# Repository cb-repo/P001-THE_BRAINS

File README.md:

# THE BRAINS v4.0

THE BRAINS is an compact and lightweight dual DC-motor ESC: originally designed for antweight combat robots, but is suitable for any appliction requiring a lightweight motor driver.

Designed and built in [Christchurch, New Zealand ](https://www.google.co.nz/maps/place/Christchurch+New+Zealand) by Connor Benton, visit [cb-technology](https://www.cb-technology.co.nz/) for details.

## FEATURES

- 2x Bi-Directional DC motor outputs.
- 2x Signal output channels for additional electroncis (BLDC ESC, servo, etc).
- Status LED's to indicate run mode, faults and calibration.
- Under-voltage, over-current, over-temperature, and reverse polarity protections.
- Internal BEC to provide power to the radio reciever.
- Failsafe checks for loss of connection with radio.
- Auto-Detection of different radio protocols on the same input.
- Instant brown-out recovery.
- Calibrate function to customise drive mode, channel mapping, and channel inversion.
- Includes a 100nF capacitor across each motor to filter noise and voltage spikes.

## SPECIFICATIONS

- **Dimensions:** 25x19x3 mm
- **Weight:** 2g *excluding wires*
- **Input Voltage - Rated:** 2S lipo (6-10.4V)
- **Input Voltage - Max:** 12.0V
- **Motor Output:** 2.1A cont (3A peak) per channel 
- **BEC:** 5V, 80mA. Designed to power the radio reciever but no motors or servos
- **Signal Input:** Servo PWM, PPM, IBUS, SBUS
- **Signal Mixing:** Onboard signal mixing for TANK/ARCADE drive styles and channel mapping + inverting
- **Signal Output:** Servo PWM 
   
## Status LEDs
There are two LEDs on THE BRAINS (1x red, 1x green) and the behaviour of each indicate what state the device is in.
 - **Normal Operation** Green: ON, Red: OFF
 - **Fault Conditions**
    - **Signal-Input** Green: FLASH, Red: OFF
    - **Under-Voltage** Green: OFF, Red: FLASH (1Hz)
    - **Over-Temperature** Green: OFF, Red: FAST FLASH (5Hz)
 - **Calibration** Green: PATTERN, Red: PATTERN. (See Calibration section for specific LED patterns) 

## Fault Conditions
In all of the following fault conditions, all drive/output signals are stopped no matter the input signals. Once the fault condition is resolved, functionality will resume immediately. 
 - **Under-Voltage:** An under-voltage event occurs if the battery voltage falls below 3.2V (per cell). 
 - **Over-Temperature:** An over-temperature event occurs when the temperature sense circuit on THE BRAINS reaches 100°C.
 - **Signal-Input:** A signal-input fault occurs if the signal between the THE BRAINS and the radio reciever is lost. Note: You still need to set the failsafe on the radio reciever to detect loss of connection with the transmitter.

## Calibration
###### Calibration Parameters
THE BRAINS has a number of calibration parateters that are can be chosen from, these are:
- **Input Signal:**
At no point should the operator have to manually set the protocol, this will be auto-detected without the operator knowing.
    - Servo PWM (standard 1-2ms pulse)
    - PPM
    - IBUS
    - SBUS
- **Driving Mode:**
    - Tank (Each motor speed is controlled by a different input)
    - Arcade (One input controls both motor speeds and another is mixed in to control the steering) 
- **Signal Mapping:**
    - Any input channel can be mapped to any of the 4 outputs (2x motors + 2x signal output). 
    - Any channel can be reversed (usually auto-detected during the calibration procedure). 

The default calibration parameters are:
- **Input Signal:** SBUS
- **Driving Mode:** TANK
- **Signal Mapping:** 
     - Ch1 = Motor1, 
     - Ch2 = Motor2,
     - Ch3 = Servo1,
     - Ch4 = Servo2,

###### Calibration Procedure
 1. Ensure the transmitter is turned ON, it has been bound to the radio reciever, and all sticks are in their zero (neutral) position.

 2. Plug the radio reciever and motors into THE BRAINS. 
 It is important that the motors are connected in the orientation used for the final robot, this will allow auto-detection of the channel mapping and inversion during the following Simon-says process.

 3. Turn THE BRAINS ON and, within 10 seconds, trigger the calibration procedure using one of the following:
    - Short-circuit the two calibration pads on the underside. 
    These pads are the two circular pads close together and circled with silkscreen.
    - Wiggle any input on the transmitter back and forward 10 times. 
    Make sure to push the stick from CENTER all the way to MAX/MIN when wiggling. 

 4. Both status LEDs will pulse 10 times and then stay fully illumintaed to indicated THE BRAINS has entered CALIBRATION mode and is ready to begin the Simon-Says process. 

 5. When ready, push any stick on the transmitter to MAX and back to CENTER.
 The rest of the calibration happens pretty quickly so please read, and understand, steps 6 + 7 before proceeding. 

 6. Both status LED's will turn OFF and the Simon-says motor calibration procedure is started. 
    - Two tests are run, each will twitch the two motors and cause the robot to move forward, reverse, left, or right. 
    The user must then input that motion back into the remote. eg:
        - Robot twitches forward: Tank drive, simualtaneously push both sticks forward. Arcarde drive, push one stick forward.
        - Robot twitches left: Tank drive, simualtaneously push left stick back and right forward. Arade drive, push one stick left
    - The process for each test is:
        1. Both LED's turn OFF
        2. The motor twitches
        3. Red LED turns ON
        4. User presses input(s) to MAX/MIN
        5. Green LED turns ON 
        6. User returns input(s) back to CENTER
        7. Both LED's pulse 3 times to indicate success
        8. Repeat for second test

 7. Both status LED's will again turn OFF and the Simon-says output signal calibration procedure is started. 
    - Two more tests are run to map the inputs to the Signal 1 and 2 outputs. The primary difference with this test is that no motor are driven, THE BRAINS is just monitoring the inputs.
    - The process for each test is:
        1. Both LED's will momentrarily turn OFF to indicate the test has started
        2. Red LED turns ON
        3. User presses the input (to MAX/MIN) they want mapped to output signal 1
        4. Green LED turns ON
        5. User returns input back to CENTER 
        6. Both LED's pulse 3 times to indicate success
        7. Repeat for output signal 2.

 12. Calibration Complete
     - Both status LEDs will pulse 10 times to indicate a successfull calibration.
     - Once the LED pulses are complete, THE BRAINS immediately enter Run mode with the new calibration.
     - If THE BRAINS is turned OFF before completing the calibration process, NONE of the new parameters are stored and it will revert to the previous configuraion.

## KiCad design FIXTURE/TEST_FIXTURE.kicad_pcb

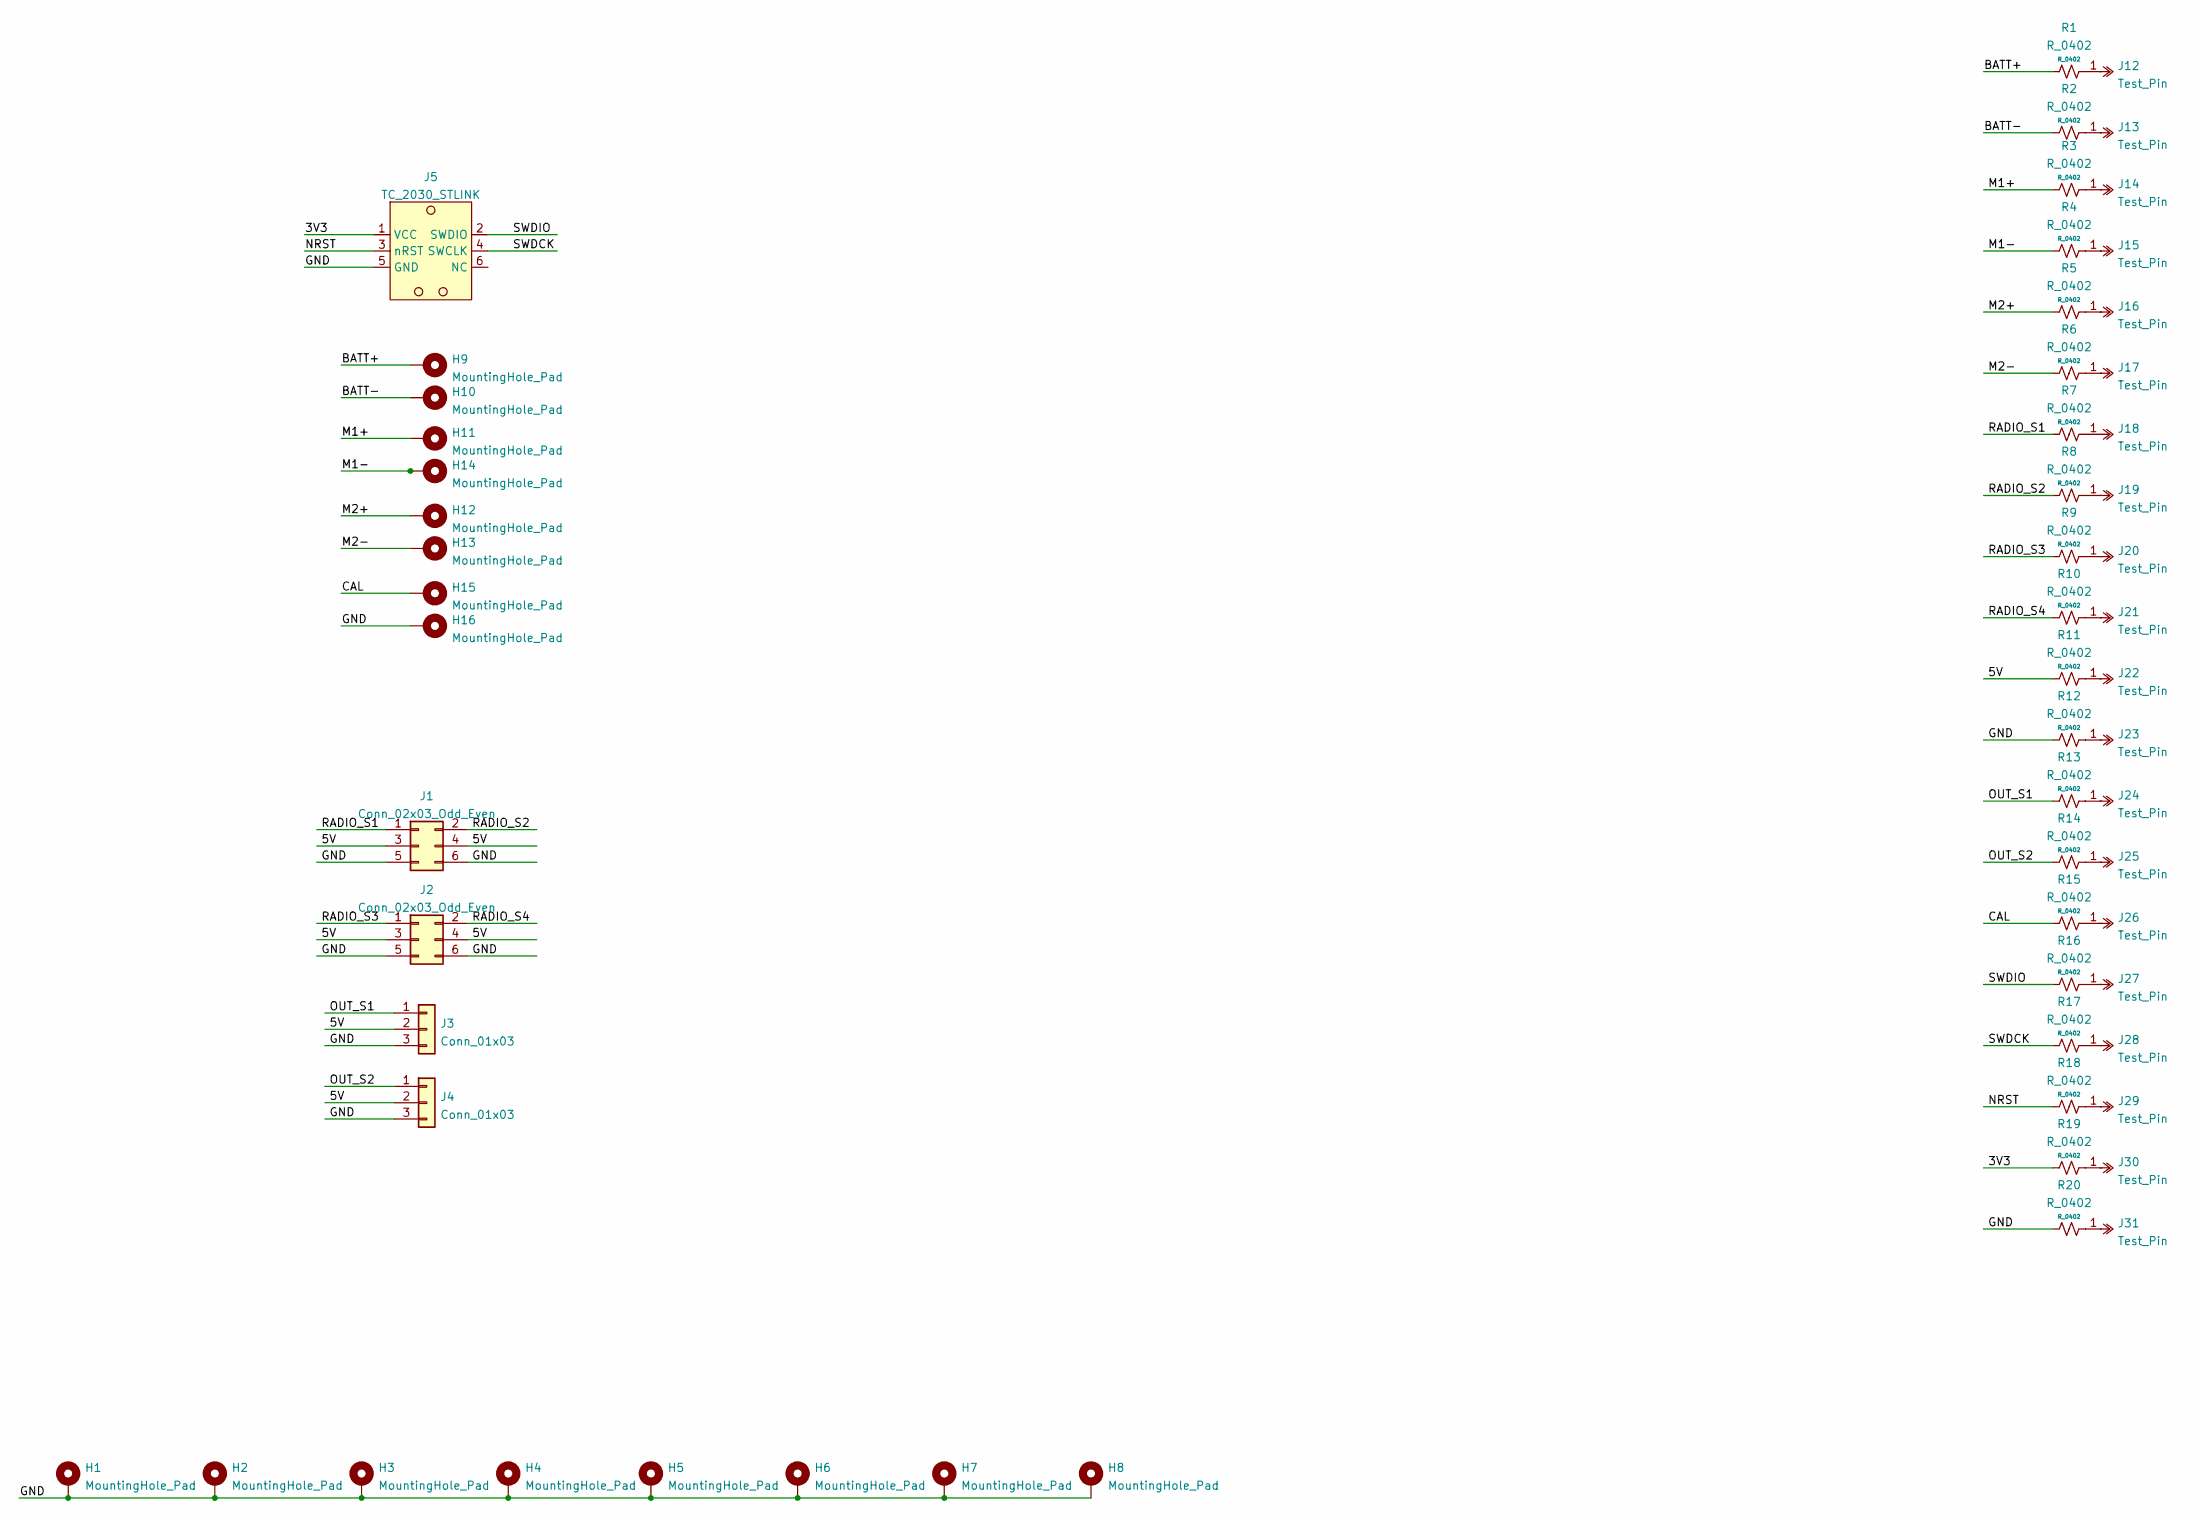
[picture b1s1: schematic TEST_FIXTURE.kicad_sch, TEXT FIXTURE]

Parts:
H1, H2, H3, H4, H5, H6, H7, H8, H9, H10, H11, H12, H13, H14, H15, H16: MountingHole_Pad; MountingHole_3mm_Pad_TopBottom
J1, J2: Conn_02x03_Odd_Even; PinHeader_2x03_P2.54mm_Vertical
J3, J4: Conn_01x03; PinHeader_1x03_P2.54mm_Horizontal
J5: TC_2030_STLINK; Tag-Connect_TC2030-IDC-FP_2x03_P1.27mm_Vertical
J12, J13, J14, J15, J16, J17, J18, J19, J20, J21, J22, J23, J24, J25, J26, J27, J28, J29, J30, J31: Test_Pin; R-2-SC
R1, R2, R3, R4, R5, R6, R7, R8, R9, R10, R11, R12, R13, R14, R15, R16, R17, R18, R19, R20: R_0402

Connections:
/3V3: J5.1 (VCC), R19.1
/5V: J1.3, J1.4, J2.3, J2.4, J3.2, J4.2, R11.1
/BATT+: H9.1, R1.1
/BATT-: H10.1, R2.1
/CAL: H15.1, R15.1
/GND: H1.1, H2.1, H3.1, H4.1, H5.1, H6.1, H7.1, H8.1, H16.1, J1.5, J1.6, J2.5, J2.6, J3.3, J4.3, J5.5 (GND), R12.1, R20.1
/M1+: H11.1, R3.1
/M1-: H14.1, R4.1
/M2+: H12.1, R5.1
/M2-: H13.1, R6.1
/NRST: J5.3 (nRST), R18.1
/OUT_S1: J3.1, R13.1
/OUT_S2: J4.1, R14.1
/RADIO_S1: J1.1, R7.1
/RADIO_S2: J1.2, R8.1
/RADIO_S3: J2.1, R9.1
/RADIO_S4: J2.2, R10.1
/SWDCK: J5.4 (SWCLK), R17.1
/SWDIO: J5.2 (SWDIO), R16.1
unnamed: J12.1, R1.2
unnamed: J13.1, R2.2
unnamed: J14.1, R3.2
unnamed: J15.1, R4.2
unnamed: J16.1, R5.2
unnamed: J17.1, R6.2
unnamed: J18.1, R7.2
unnamed: J19.1, R8.2
unnamed: J20.1, R9.2
unnamed: J21.1, R10.2
unnamed: J22.1, R11.2
unnamed: J23.1, R12.2
unnamed: J24.1, R13.2
unnamed: J25.1, R14.2
unnamed: J26.1, R15.2
unnamed: J27.1, R16.2
unnamed: J28.1, R17.2
unnamed: J29.1, R18.2
unnamed: J30.1, R19.2
unnamed: J31.1, R20.2

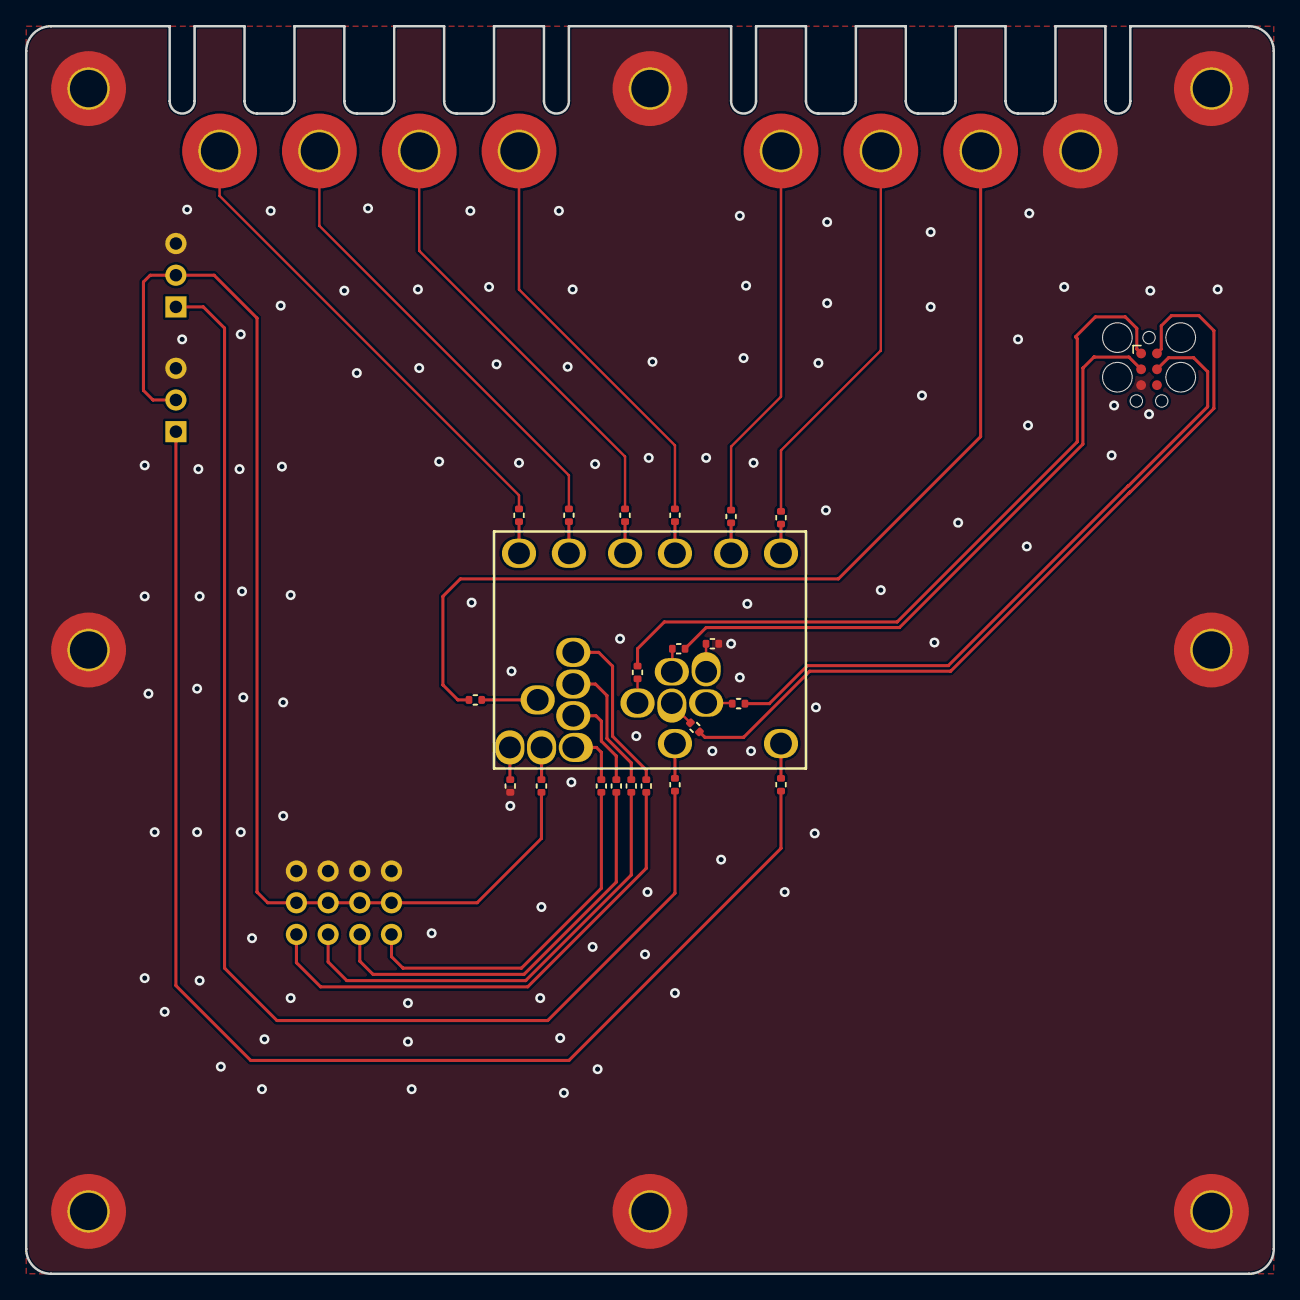
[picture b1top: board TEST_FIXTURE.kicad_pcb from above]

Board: 2 copper layers, 100.0 x 100.0 mm, 61 parts (0 on the bottom side), 39 nets.

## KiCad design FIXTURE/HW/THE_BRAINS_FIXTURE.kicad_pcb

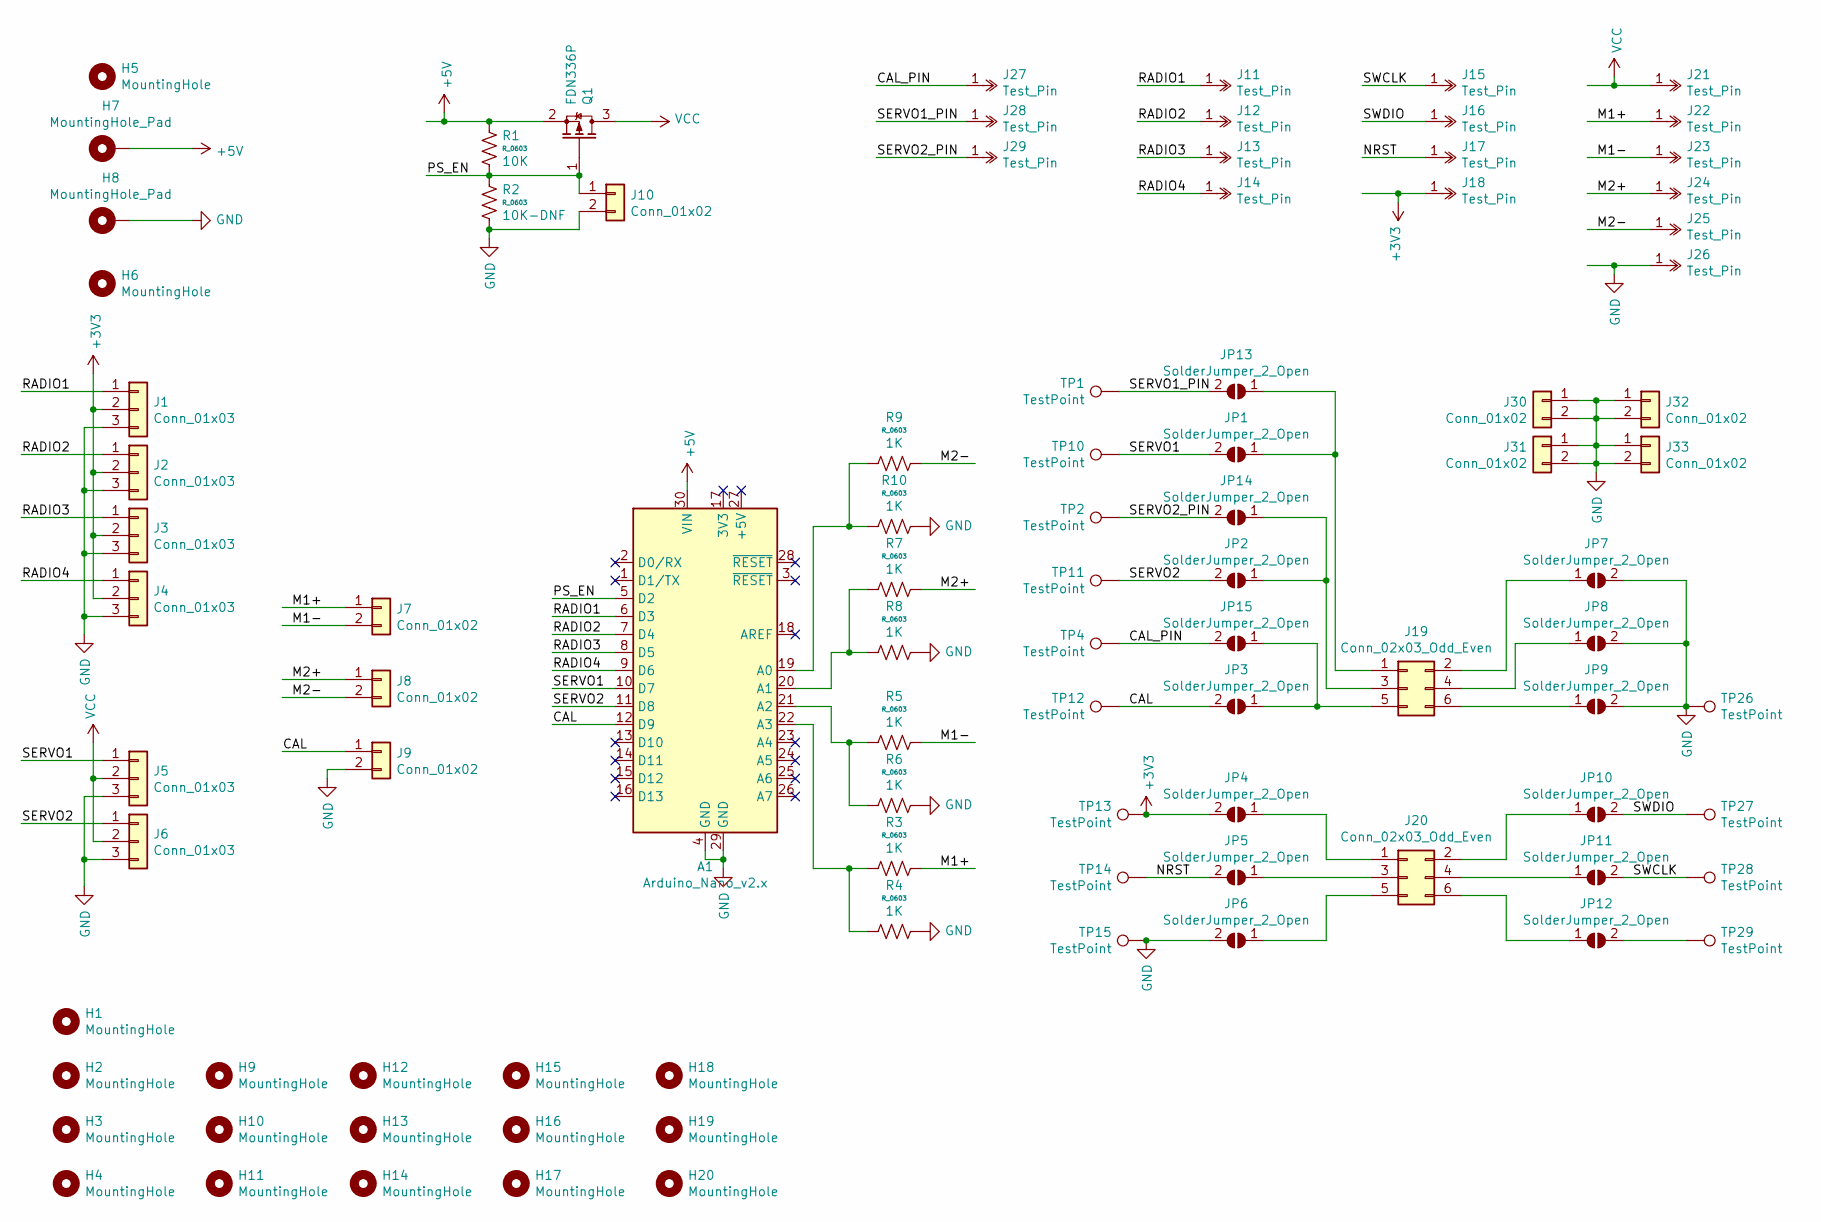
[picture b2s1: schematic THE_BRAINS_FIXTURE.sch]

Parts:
A1: Arduino_Nano_v2.x; Arduino_Nano_WithMountingHoles
H1, H2, H3, H4: MountingHole; MountingHole_6mm
H5, H6: MountingHole; MountingHole_3mm
H7, H8: MountingHole_Pad; MountingPad_4.0x3.0mm
H9, H10, H11, H12, H13, H14, H15, H16, H17, H18, H19, H20: MountingHole; MountingHole_3.2mm_M3
J1, J2, J3, J4: Conn_01x03; PinHeader_1x03_P2.54mm_Vertical
J5, J6: Conn_01x03; PinHeader_1x03_P2.54mm_Horizontal
J7, J8, J9, J10: Conn_01x02; PinHeader_1x02_P2.54mm_Horizontal
J11, J12, J13, J14: Test_Pin; R-2-SC
J15, J16, J17, J18, J21, J22, J23, J24, J25, J26, J27, J28, J29: Test_Pin; R-0-SC
J19, J20: Conn_02x03_Odd_Even; IDC-Header_2x03_P2.54mm_Vertical
J30, J31, J32, J33: Conn_01x02; PinHeader_1x02_P2.54mm_Vertical
JP1, JP2, JP3, JP4, JP5, JP6, JP7, JP8, JP9, JP10, JP11, JP12, JP13, JP14, JP15: SolderJumper_2_Open; SolderJumper-2_P1.3mm_Open_RoundedPad1.0x1.5mm
Q1: FDN336P; SOT-23
R1, R2, R3, R4, R5, R6, R7, R8, R9, R10: R_0603
TP1, TP2, TP4, TP10, TP11, TP12, TP13, TP14, TP15, TP26, TP27, TP28, TP29: TestPoint; TestPoint_Loop_D2.50mm_Drill1.0mm

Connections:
+3V3: J1.2, J2.2, J3.2, J4.2, J18.1, JP4.2 (B), TP13.1
+5V: A1.30 (VIN), H7.1, Q1.2 (S), R1.1
/CAL: A1.12 (D9), J9.1, JP3.2 (B), TP12.1
/CAL_PIN: J27.1, JP15.2 (B), TP4.1
/M1+: J7.1, J22.1, R3.2
/M1-: J7.2, J23.1, R5.2
/M2+: J8.1, J24.1, R7.2
/M2-: J8.2, J25.1, R9.2
/NRST: J17.1, JP5.2 (B), TP14.1
/RADIO1: A1.6 (D3), J1.1, J11.1
/RADIO2: A1.7 (D4), J2.1, J12.1
/RADIO3: A1.8 (D5), J3.1, J13.1
/RADIO4: A1.9 (D6), J4.1, J14.1
/SERVO1: A1.10 (D7), J5.1, JP1.2 (B), TP10.1
/SERVO1_PIN: J28.1, JP13.2 (B), TP1.1
/SERVO2: A1.11 (D8), J6.1, JP2.2 (B), TP11.1
/SERVO2_PIN: J29.1, JP14.2 (B), TP2.1
/SWCLK: J15.1, JP11.2 (B), TP28.1
/SWDIO: J16.1, JP10.2 (B), TP27.1
unnamed: A1.19 (A0), R9.1, R10.1
unnamed: A1.20 (A1), R7.1, R8.1
unnamed: A1.21 (A2), R5.1, R6.1
unnamed: A1.22 (A3), R3.1, R4.1
unnamed: J19.1, JP1.1 (A), JP13.1 (A)
unnamed: J19.2, JP7.1 (A)
unnamed: J19.3, JP2.1 (A), JP14.1 (A)
unnamed: J19.4, JP8.1 (A)
unnamed: J19.5, JP3.1 (A), JP15.1 (A)
unnamed: J19.6, JP9.1 (A)
unnamed: J20.1, JP4.1 (A)
unnamed: J20.2, JP10.1 (A)
unnamed: J20.3, JP5.1 (A)
unnamed: J20.4, JP11.1 (A)
unnamed: J20.5, JP6.1 (A)
unnamed: J20.6, JP12.1 (A)
unnamed: JP12.2 (B), TP29.1
VCC: J5.2, J6.2, J21.1, Q1.3 (D)

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
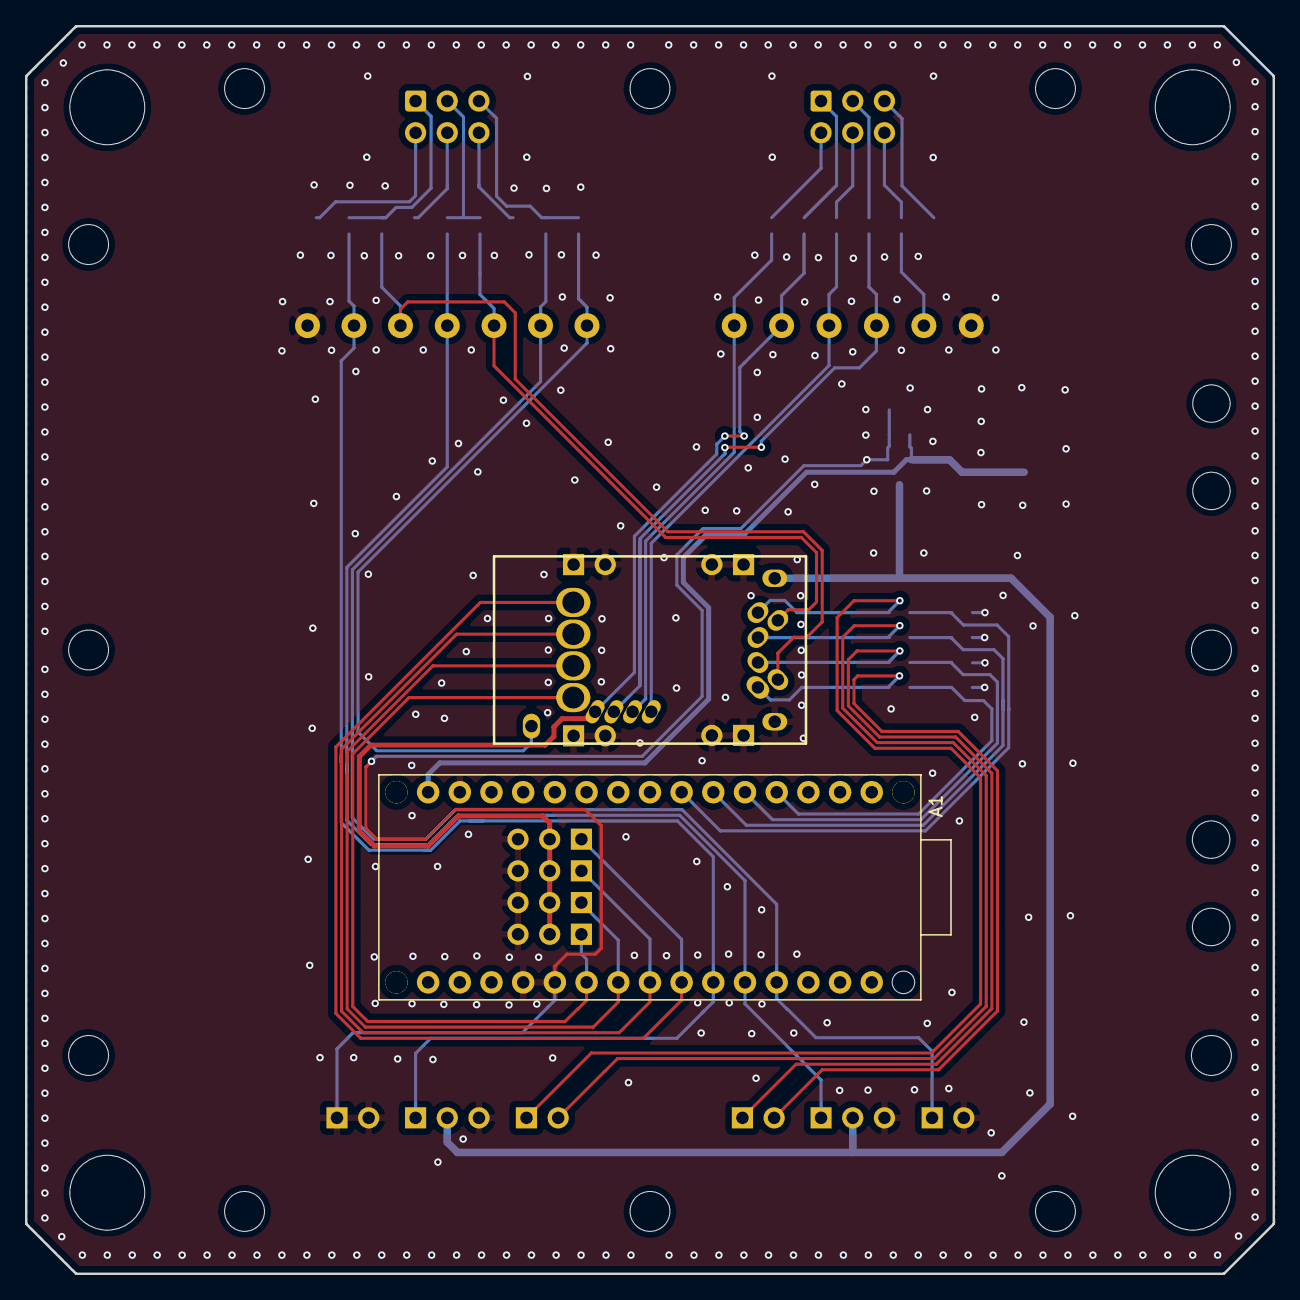
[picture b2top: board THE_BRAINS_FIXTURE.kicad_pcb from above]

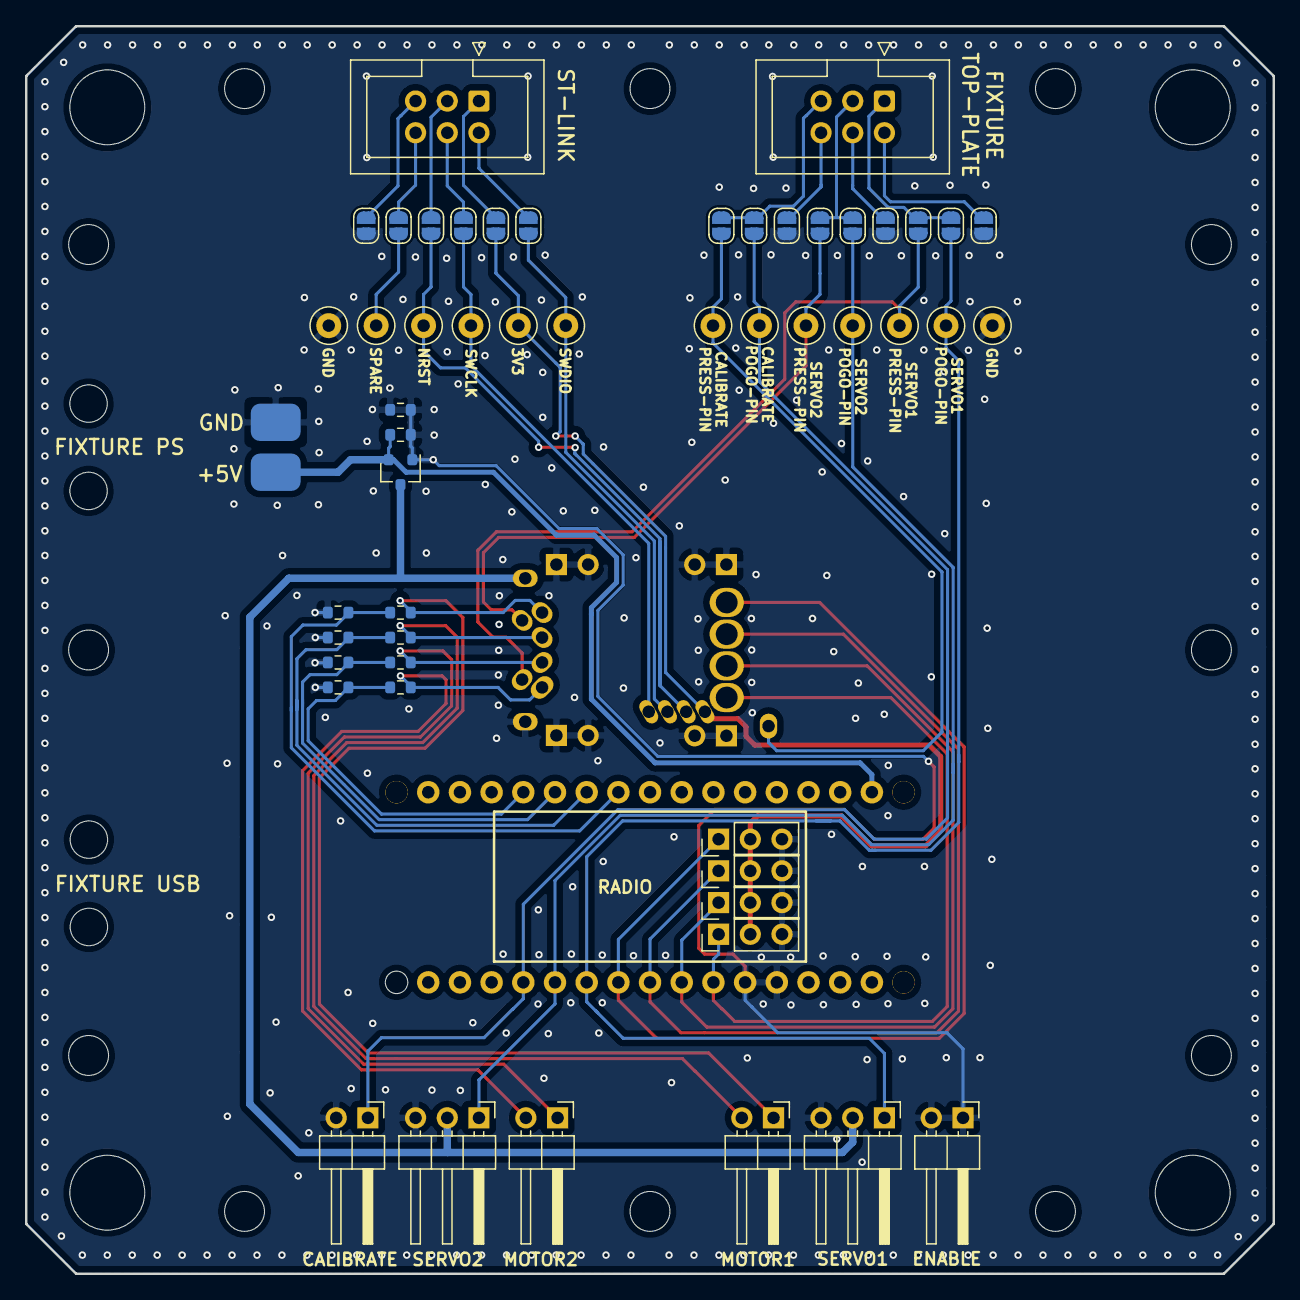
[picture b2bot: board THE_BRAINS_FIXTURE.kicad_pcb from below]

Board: 2 copper layers, 100.0 x 100.0 mm, 95 parts (57 on the bottom side), 38 nets.

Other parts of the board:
H5#2, H6#2: MountingHole; MountingHole_3mm

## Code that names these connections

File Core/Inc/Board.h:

/* ~~~~~~~~~~~~~~~~~~~~~~~~~~~~~~~~~~~~~~~~~~~~~~~~~~ */
#ifndef BOARD_H
#define BOARD_H
/* ~~~~~~~~~~~~~~~~~~~~~~~~~~~~~~~~~~~~~~~~~~~~~~~~~~ */

// CONFIG INTERRUPT
#define USE_GPIO_IRQS
#define USE_EXTI_8
#define USE_EXTI_9
#define USE_EXTI_10
#define USE_EXTI_15

// CONFIG TIMERS
#define USE_TIM_IRQS
// Motor
#define USE_TIM2
#define TIM_MOTOR TIM_2
#define TIM_MOTOR_AF		GPIO_AF2_TIM2
#define TIM_MOTOR_RELOAD 	255
#define TIM_MOTOR_FREQ		(MOTOR_FREQ*(TIM_MOTOR_RELOAD+1))
// Radio
#define USE_TIM6
#define TIM_RADIO 			TIM_6
#define TIM_RADIO_RELOAD 	0xffff
#define TIM_RADIO_FREQ		1000000
// Servo
#define USE_TIM21
#define TIM_SERVO1 			TIM_21
#define TIM_SERVO1_RELOAD 	(10*1000)
#define TIM_SERVO1_FREQ		1000000
// Wepon
#define USE_TIM22
#define TIM_SERVO2 			TIM_22
#define TIM_SERVO2_RELOAD 	(10*1000)
#define TIM_SERVO2_FREQ		1000000

// CONFIG LED
// Pin3 (PC14) - Status/Green
// Pin10 (PA0) - Fault/Red
#define LED_STATUS_GPIO		GPIOC
#define LED_STATUS_PIN		GPIO_PIN_14
#define LED_FAULT_GPIO		GPIOA
#define LED_FAULT_PIN		GPIO_PIN_0

// CONFIG RADIO
// Pin31 (PA10) - RadioS1
// Pin30 (PA9) - RadioS2
// Pin29 (PA8) - RadioS3
// Pin28 (PB15) - RadioS4

#define RADIO_S1_GPIO		GPIOA
#define RADIO_S1_PIN		GPIO_PIN_10
#define RADIO_S2_GPIO		GPIOA
#define RADIO_S2_PIN		GPIO_PIN_9
#define RADIO_S3_GPIO		GPIOA
#define RADIO_S3_PIN		GPIO_PIN_8
#define RADIO_S4_GPIO		GPIOB
#define RADIO_S4_PIN		GPIO_PIN_15

// CONFIG DC-MOTOR
// Pin38 (PA15) - MotorL_PWM1
// Pin39 (PB3) - MotorL_PWM2
// Pin45 (PB8) - MotorL_nSLEEP
// Pin21 (PB10) - MotorR_PWM1
// Pin22 (PB11) - MotorR_PWM2
// Pin10 (PB2) - MotorR_nSLEEP
#define USE_DRV8212
#define MOTOR_LnSLEEP_GPIO	GPIOB
#define MOTOR_LnSLEEP_PIN	GPIO_PIN_8
#define MOTOR_RnSLEEP_GPIO	GPIOB
#define MOTOR_RnSLEEP_PIN	GPIO_PIN_2
#define MOTOR_LPWM1_GPIO	GPIOA
#define MOTOR_LPWM1_PIN		GPIO_PIN_15
#define MOTOR_LPWM1_CH		0
#define MOTOR_LPWM2_GPIO	GPIOB
#define MOTOR_LPWM2_PIN		GPIO_PIN_3
#define MOTOR_LPWM2_CH		1
#define MOTOR_RPWM1_GPIO	GPIOB
#define MOTOR_RPWM1_PIN		GPIO_PIN_10
#define MOTOR_RPWM1_CH		2
#define MOTOR_RPWM2_GPIO	GPIOB
#define MOTOR_RPWM2_PIN		GPIO_PIN_11
#define MOTOR_RPWM2_CH		3

// CONFIG SERVO
// Pin11 (PA1) - Servo1
// Pin2 (PC13) - Servo2
#define SERVO1_GPIO			GPIOA
#define SERVO1_PIN			GPIO_PIN_1
#define SERVO2_GPIO			GPIOC
#define SERVO2_PIN			GPIO_PIN_13

#endif /* BOARD_H */
/* ~~~~~~~~~~~~~~~~~~~~~~~~~~~~~~~~~~~~~~~~~~~~~~~~~~ */

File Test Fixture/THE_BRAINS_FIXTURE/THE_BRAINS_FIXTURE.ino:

#include <Servo.h> 

Servo radioS1;
Servo radioS2;
Servo radioS3;
Servo radioS4;
Servo servoS1;
Servo servoS2;

// RADIO PINS
#define RADIO1              1
#define RADIO2              2
#define RADIO3              3
#define RADIO4              4

// SERVO PINs
#define SERVO1              5
#define SERVO2              6
int32_t servo1 = 0;
int32_t servo2 = 0;

// SERVO POSITIONS
#define SERVO_LOW           0
#define SERVO_MID           90
#define SERVO_MAX           180

// STATE MACHINE
#define STATE_IDLE          0
#define STATE_POWERSUPPLY   1
#define STATE_RADIO         2
#define STATE_MOTOR         3
int32_t state = STATE_IDLE;


void setup() {
    //INIT RADIO
    radioS1.attach(RADIO1);
    radioS2.attach(RADIO2);
    radioS3.attach(RADIO3);
    radioS4.attach(RADIO4);
    radioS1.write(90);
    radioS2.write(90);
    radioS3.write(90);
    radioS4.write(90);
    servoS1.attach(SERVO1);
    servoS2.attach(SERVO2);
}

void loop() {
    readRadio();

    switch(state) {
      case STATE_IDLE:
        state = STATE_POWERSUPPLY;
        break;
      case STATE_POWERSUPPLY:
        testPS();
        state = STATE_RADIO;
        break;
      case STATE_RADIO:
        testRADIO();
        state = STATE_MOTOR;
        break;
      case STATE_MOTOR:
        testMOTOR();
        state = STATE_IDLE;
        break;
      default:
        state = STATE_IDLE;
        break;
    }
}

void testPS() {
    // SOMETHING
}

void testRADIO() {
    // SOMETHING
}

void testMOTOR() {
    // SOMETHING
}

void readRadio() {
    spareServo1 = servoS1.read();
    spareServo2 = servoS2.read();
}

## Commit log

2021-10-14 v3.0 manufacturing release files
2021-10-17 Added v3.0 BOM File
2021-10-17 Merged Hardware and Firmware repo
2021-10-23 Sync file structure
2021-10-27 Update micro pinout
2021-10-27 Updated motor functions
    Added config for different DRV drivers.
2021-10-27 Generate structure for tester board FW
2021-11-09 Integrate FW + HW Repo
2021-11-09 Sync Repo
2021-11-09 Re-Integrate FW + HW
2021-11-09 Sync
2021-11-10 Fixed MotorM1 AF Issue
2021-11-13 Add STM32 Lambosaurus Lib as submodule
2021-11-13 Update STM32 hal Lib
2021-12-16 Added Radio Input Config (WIP)
2022-01-23 FW Update
2022-01-23 Fixture PCB Upload
2022-02-27 Sync Latest WIP Changes
2022-03-21 Make changes to all files for stable build
2022-04-15 Update all functional modules - Untested
2022-04-15 Sync Mech + HW stuff
2022-04-19 Calibration Code Working
2022-05-24 Update Input signal spec
2022-05-24 Remove installation chapter
2022-06-07 Remove Temp HW files from repo
2022-07-25 Start Updating Readme for v3.1
2022-08-16 Redisign with fingers for I/O and add 5V O/P
2022-11-07 Move Radio.c/.h to Dedicated Radio Protocol Lib
2022-11-07 Import Project onto Linux Machine
2022-11-09 Port Existing Codebase to THE_BRAINS v4.0
2022-11-15 Fix Battery Detect ADC Channel
2022-11-15 Implement Updated System Module - WIP
2022-11-21 Work on all modules to get MVP to send to CRNZ for eval
2022-11-21 Fix Default Radio Configuration from PPM to PWM
2023-02-04 Changes that were on laptop
2023-03-07 Fix PPM and IBUS Implementation Bugs
2023-03-07 Add Radio AutoDetect All The Time when No Radio Detected
2023-03-07 Update Calibrate Function to Include Radio Auto-Detect
2023-03-13 Update Whole Calibration Sequence and Add Comments Throughout Module
2023-03-19 Fix Calibration Sequence Issues and Reimplement Temperature Detect
2023-03-31 Implement Control For DRV8837 + Fix Motor Output Disparity
2023-03-31 Reduce Calibration Motor Twitch Duration
    Bots were suiciding off the desk during calibration
2023-04-03 Fix Bug With Tank Calibration Procedure
2023-04-05 CRNZ v4.0 PCB 40-off Order
2023-04-05 Fix Radio Auto Detect Issue
2023-05-22 Update Readme Documentation for v4.0 Release
2023-05-22 Update Readme Section Titles
2023-05-22 Resolve .jpg/.png asset issue
2023-05-22 Ready for Documentation Release to CRNZ
2023-08-29 WIP Laptop Update Commit
2024-06-04 Update gitignore
2024-06-05 Create Packaging Label
2024-06-11 Added submodule FW/L001-RadioProtocols
2024-06-15 Build FW for DRV8212
